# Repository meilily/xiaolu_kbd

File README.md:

Xiaolu Keyboard
===============

この Xiaolu Keyboard は、[Seeed XIAO RP2040](https://akizukidenshi.com/catalog/g/g117044/) を使用した小型の自作キーボードです。このキーボードは、テンキーやゲーム用のマクロキーボードなどとして使用できる、コンパクトで手のひらサイズのデバイスとして設計されています。キーボードには、4×4グリッドに配置された合計16個の小さなキーが使用されています。

このキーボードを作るには、基本的なハンダ付けの技術と工具、そしてSeeed Xiao用にファームウェアをビルドしてインストールする必要があります。必要なものがすべて揃ったら、ビルドガイドを参照してください。

キーボードの組み立てに成功したら、ArduinoやQMKなどのファームウェアを使って、独自のマクロやカスタム機能でキーボードをプログラムすることができます。Arduinoのサンプルファームウェアでは、例としてシンプルな4x4のテンキー機能を提供しています。

## 特徴

* 秋月C基板互換サイズでコンパクトで手のひらサイズ (51mm x 76mm)
* Switronic TS-AGGNH-G プッシュボタンの採用により小型ながらもキースイッチの押しやすさを両立
* MCU として Seeed XIAO を採用

## 手順書

* [パーツリスト](docs/bom.md)
* [ビルドガイド](docs/building_instruction.md)
* [拡張機能](docs/extensible_features.md)

## 外観図

## License

licensed under the [CC-BY-SA-4.0](https://creativecommons.org/licenses/by-sa/4.0/) except for QMK.
QMK firmware source code is licensed under the [GPLv2](https://www.gnu.org/licenses/old-licenses/gpl-2.0.html)

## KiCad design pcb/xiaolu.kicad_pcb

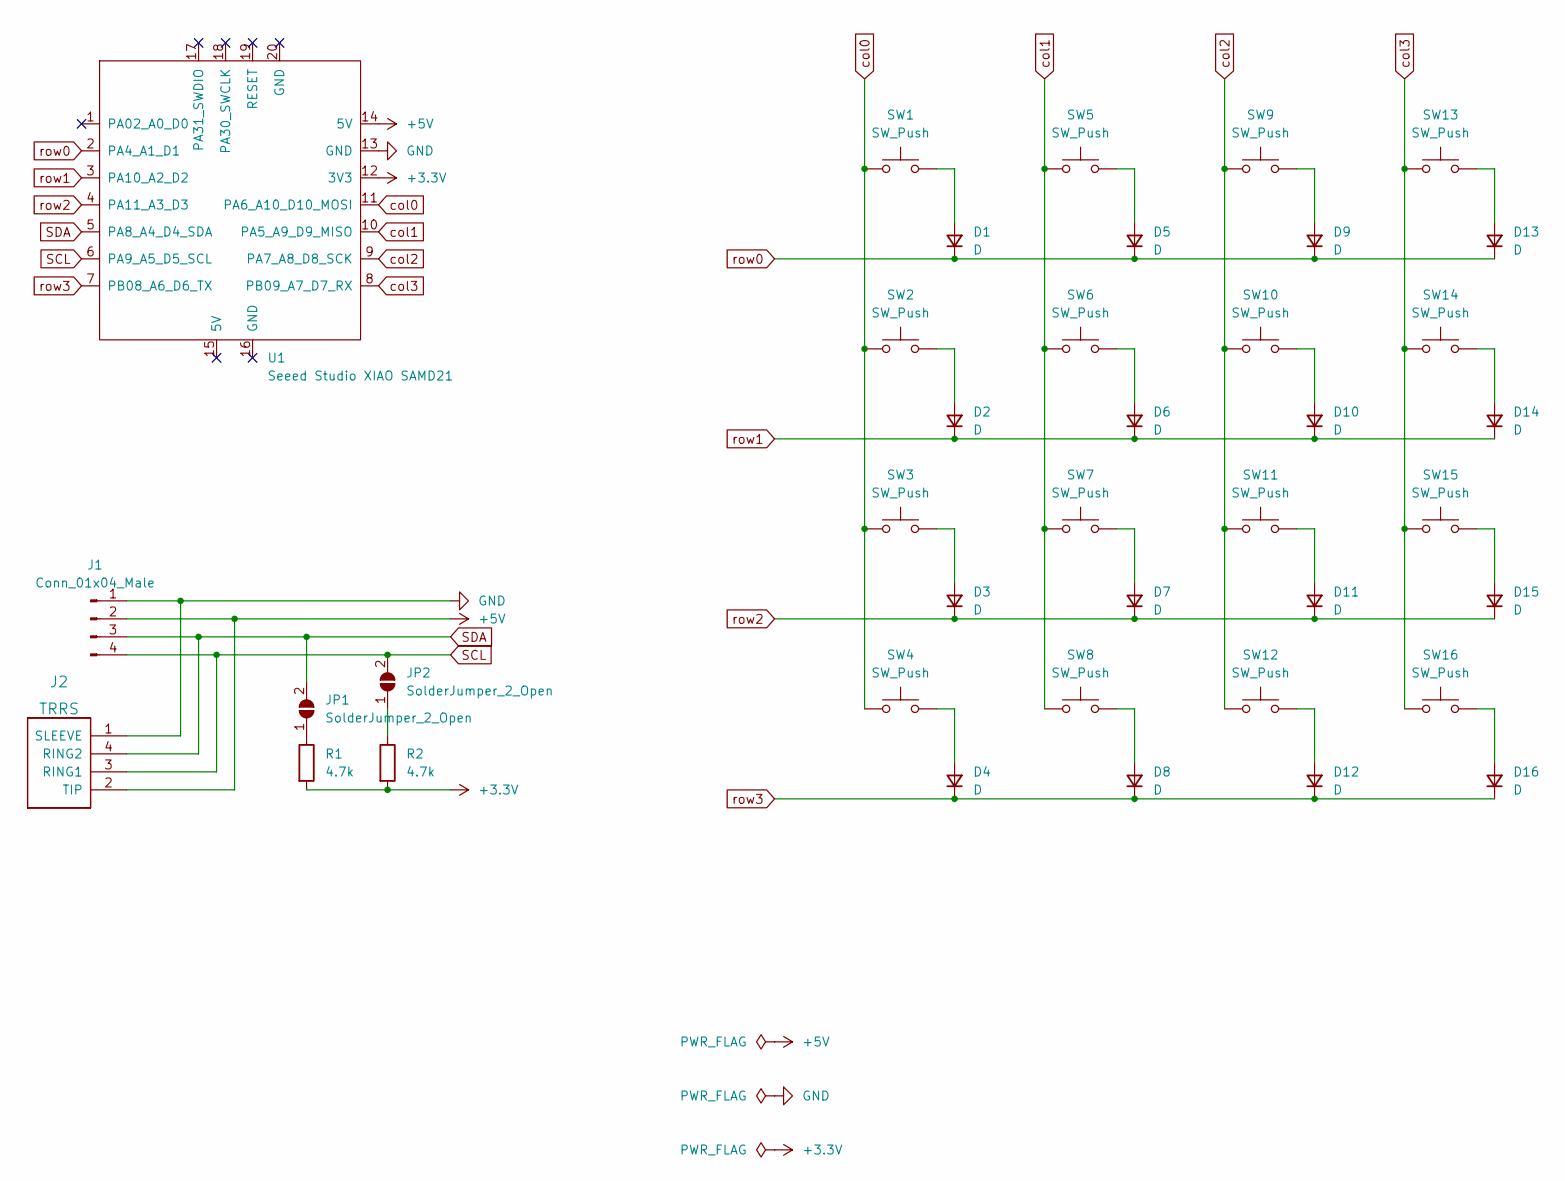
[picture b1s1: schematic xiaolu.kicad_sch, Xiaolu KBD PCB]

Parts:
D1, D2, D3, D4, D5, D6, D7, D8, D9, D10, D11, D12, D13, D14, D15, D16: D; D_SOD-323; LCSC Part # C2128
J1: Conn_01x04_Male; NS-Tech_Grove_1x04_P2mm_Hybrid
J2: TRRS; TRRS-PJ-320A
JP1, JP2: SolderJumper_2_Open; SolderJumper-2_P1.3mm_Open_RoundedPad1.0x1.5mm
R1, R2: 4.7k; R_0402_1005Metric; LCSC Part # C25900
SW1, SW2, SW3, SW4, SW5, SW6, SW7, SW8, SW9, SW10, SW11, SW12, SW13, SW14, SW15, SW16: SW_Push; SW_PUSH_Switronic_TS-AXXXH
U1: Seeed Studio XIAO SAMD21; XIAO-Generic-Hybrid-14P-2.54-21X17.8MM

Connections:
+3.3V: R1.2, R2.2, U1.12 (3V3)
+5V: J1.2, J2.2 (TIP), U1.14 (5V)
GND: J1.1, J2.1 (SLEEVE), U1.13 (GND)
unnamed: D1.2 (A), SW1.2
unnamed: D2.2 (A), SW2.2
unnamed: D3.2 (A), SW3.2
unnamed: D4.2 (A), SW4.2
unnamed: D5.2 (A), SW5.2
unnamed: D6.2 (A), SW6.2
unnamed: D7.2 (A), SW7.2
unnamed: D8.2 (A), SW8.2
unnamed: D9.2 (A), SW9.2
unnamed: D10.2 (A), SW10.2
unnamed: D11.2 (A), SW11.2
unnamed: D12.2 (A), SW12.2
unnamed: D13.2 (A), SW13.2
unnamed: D14.2 (A), SW14.2
unnamed: D15.2 (A), SW15.2
unnamed: D16.2 (A), SW16.2
unnamed: JP1.1 (A), R1.1
unnamed: JP2.1 (A), R2.1
SCL: J1.4, J2.3 (RING1), JP2.2 (B), U1.6 (PA9_A5_D5_SCL)
SDA: J1.3, J2.4 (RING2), JP1.2 (B), U1.5 (PA8_A4_D4_SDA)
col0: SW1.1, SW2.1, SW3.1, SW4.1, U1.11 (PA6_A10_D10_MOSI)
col1: SW5.1, SW6.1, SW7.1, SW8.1, U1.10 (PA5_A9_D9_MISO)
col2: SW9.1, SW10.1, SW11.1, SW12.1, U1.9 (PA7_A8_D8_SCK)
col3: SW13.1, SW14.1, SW15.1, SW16.1, U1.8 (PB09_A7_D7_RX)
row0: D1.1 (K), D5.1 (K), D9.1 (K), D13.1 (K), U1.2 (PA4_A1_D1)
row1: D2.1 (K), D6.1 (K), D10.1 (K), D14.1 (K), U1.3 (PA10_A2_D2)
row2: D3.1 (K), D7.1 (K), D11.1 (K), D15.1 (K), U1.4 (PA11_A3_D3)
row3: D4.1 (K), D8.1 (K), D12.1 (K), D16.1 (K), U1.7 (PB08_A6_D6_TX)

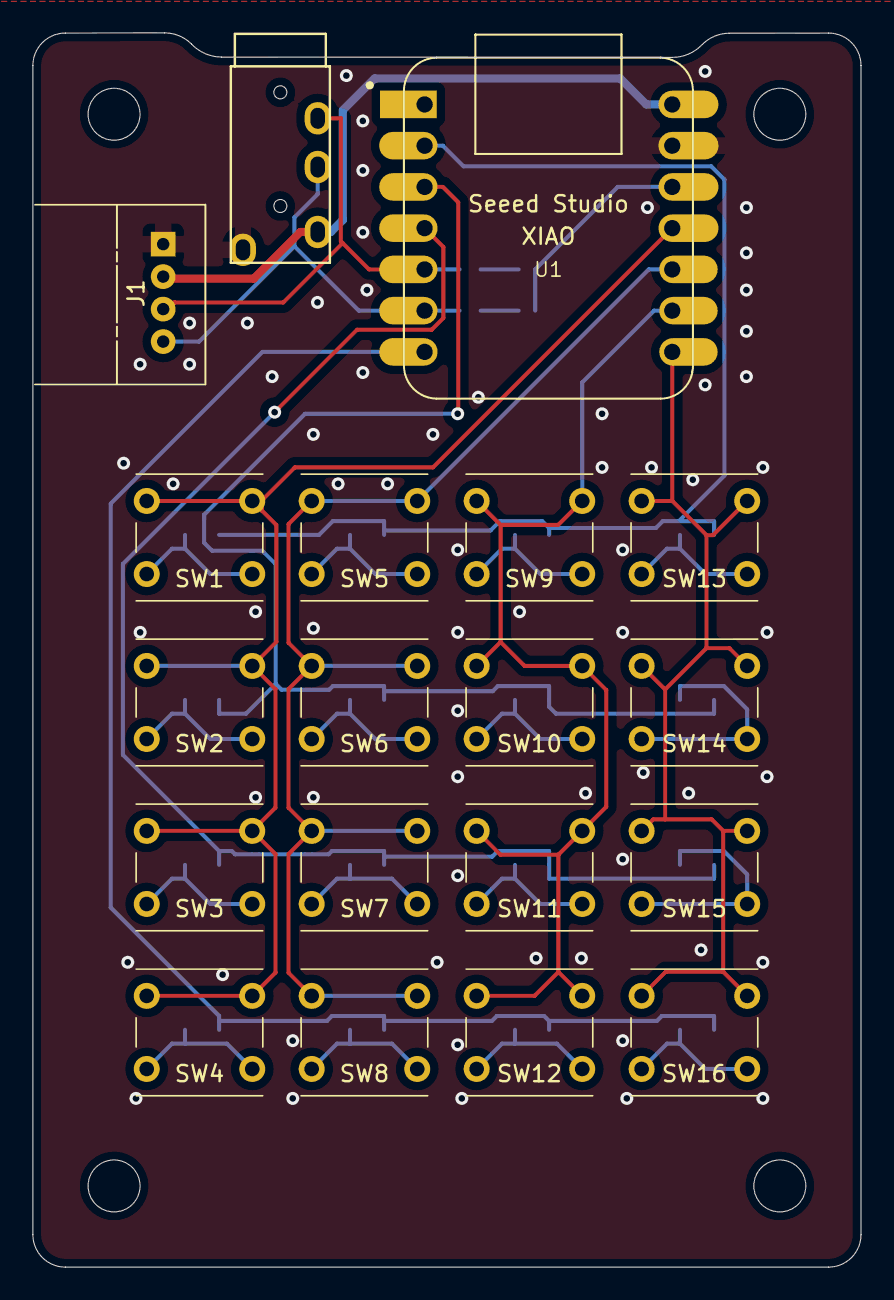
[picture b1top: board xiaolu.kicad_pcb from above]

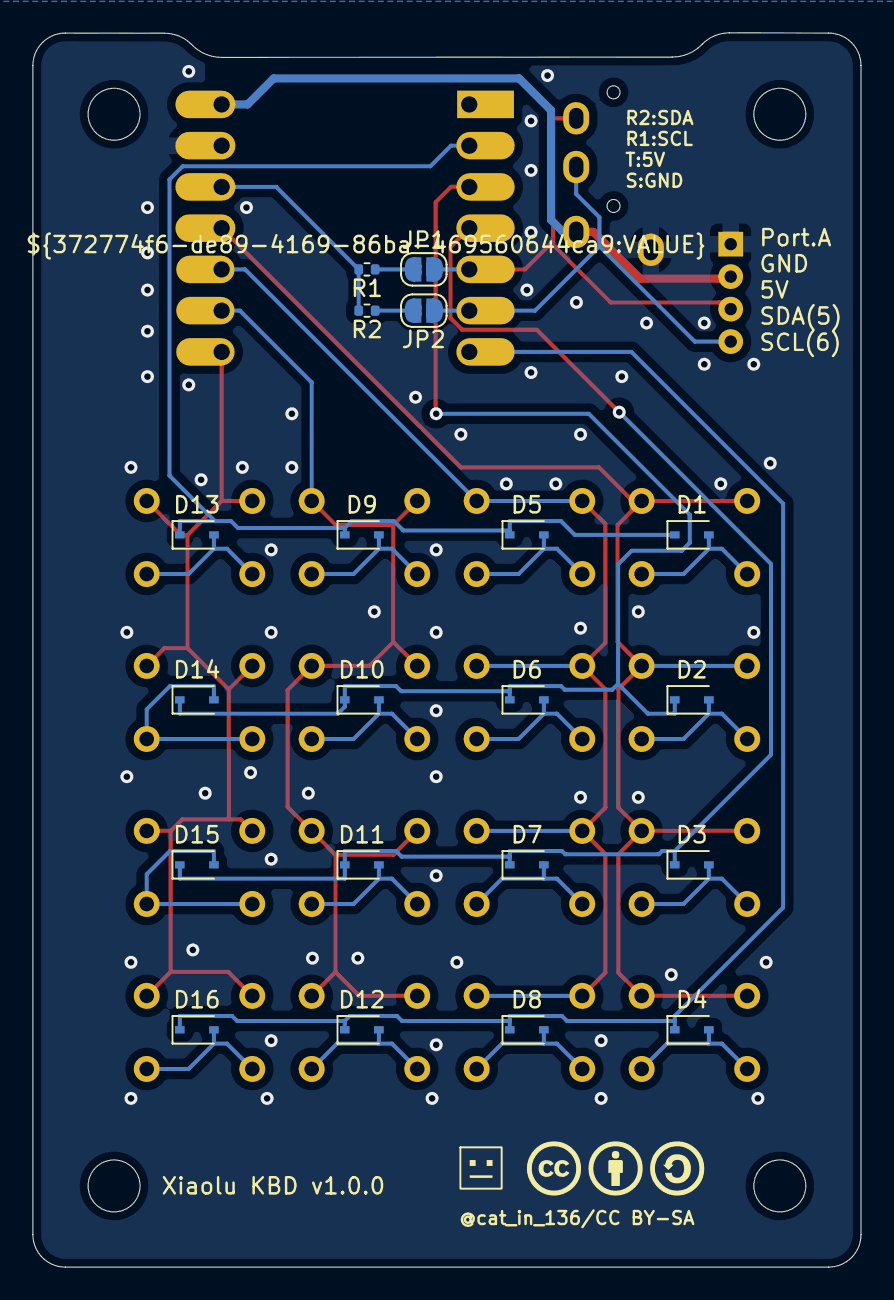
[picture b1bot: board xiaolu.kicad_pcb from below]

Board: 2 copper layers, 51.0 x 76.0 mm, 39 parts (20 on the bottom side), 31 nets.

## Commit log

2023-02-02 add .gitignore
2023-02-02 introduce pcb directory (with empty pcb design)
2023-02-05 draft schematic and board design
2023-02-05 fix TRRS symbol
2023-02-05 rename libfootprints to libfootprints.pretty
2023-02-08 replace XIAO footprint with XIAO-Generic-Hybrid-14P-2.54-21X17.8MM
2023-02-08 wiring
2023-02-17 add notch for XIAO-usb and TRRS-jack to the PCB board edge
2023-02-18 put each silk label on its internal
2023-02-18 fix Grove connector
2023-02-18 add I2C pin layout label
2023-02-18 add slikscreen logos and label
2023-02-19 use NS-Tech_Grove_1x04_P2mm_Hybrid.kicad_mod for grove connector footprint and fix the Grove connector position
2023-02-19 fix SDA/SCL pin numbers of I2C pin layout label
2023-02-21 Assign "LCSC Part #" of diodes (D1....D16) to C2128 (1N4148WS)
2023-02-24 add 3d model of XIAO RP2040
2023-02-24 add pcb/libfootprints.pretty/3dmodels/README.txt
2023-03-06 flag unconnected to unused pads of xiao
2023-03-06 fix "LCSC Part #"
2023-03-06 add optional pull-up registers to I2C SDA/SCL
2023-03-06 modify fill ground, its vias
2023-03-08 fix silk and GND vias
2023-03-08 PCB version 1.0.0
2023-04-22 add documents
2023-04-30 Update building_instruction.md with some small tips
2023-05-01 sample firmware of platfomio/arduino (maxgerhardt/platform-raspberrypi)
2023-05-02 support M5Stack CardKB Unit on platform_io arduino example FW
2023-05-02 add DEL key map of m5stack CardKB Unit on platform_io arduino example FW
2023-05-07 add QMK keyboard configurations
2023-06-03 add lasercut case design
2023-06-03 add .gitignore to /firmware/platformio_arduino
2023-06-12 sandwitch mount cheap case
2023-06-14 add sandwitch mount case to document
2023-06-15 modify README.md to remove under development notice
2023-06-17 add Platform IO/Arduino FW build guide
2023-06-18 add QMK FW build guide
2023-06-18 fix photo and License
2023-08-08 ファームウェアのアップロードに失敗する問題を修正
2023-08-09 Platform IO/Arduino手順に Git for Windows のインストールを追記
2023-08-09 ロングパス対応を手順中の注意書きから前段に移動
2023-12-24 add doc/extensible_features.md (拡張機能)
2023-12-24 Update README.md to add 特徴
2024-12-15 update bom.md of online shopping link
    - 秋月電子通商リンク更新
    - ネジ類に千石電商リンク追加
2024-12-25 Update README.md
    Adding hyperlink for more details

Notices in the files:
pcb/xiaolu.kicad_pcb:
@cat_in_136/CC BY-SA
